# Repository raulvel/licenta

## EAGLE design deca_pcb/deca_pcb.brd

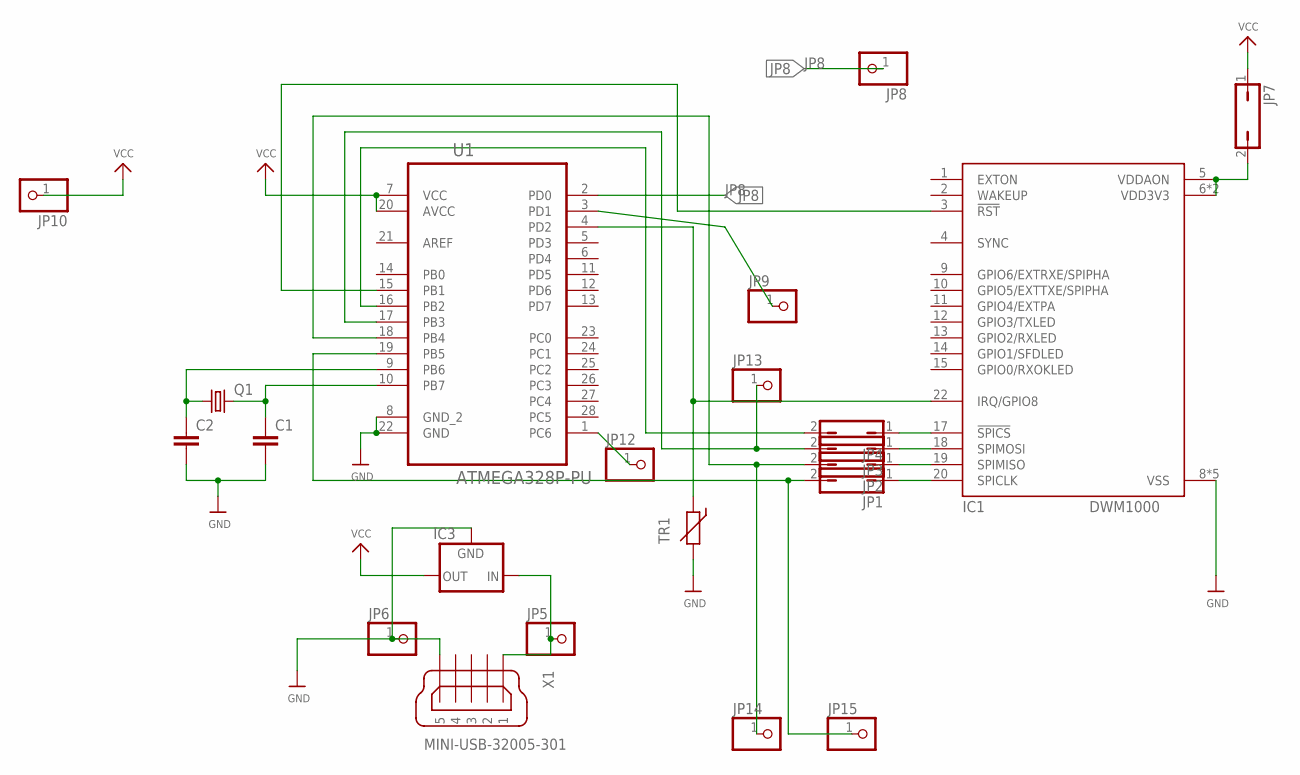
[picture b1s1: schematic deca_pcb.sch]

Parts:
C1, C2: C2.5/6; C2.5-6
IC1: DWM1000
IC3: LFXXCVS; TO220S
JP1, JP2, JP3, JP4, JP7: JP1Q; JP1
JP5, JP6, JP8, JP9, JP10, JP12, JP13, JP14, JP15: PINHD-1X1_2.54; 1X01
Q1: CRYSTALHC49S; HC49/S
TR1: THERMISTOR_R-5; R-5
U1: ATMEGA328P-PU; DIP254P762X457-28
X1: MINI-USB-32005-301; 32005-301

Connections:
GND: C1.2, C2.2, IC1.8 (VSS), IC1.16 (VSS), IC1.21 (VSS), IC1.23 (VSS), IC1.24 (VSS), IC3.2 (GND), JP6.1, TR1.2, U1.8 (GND_2), U1.22 (GND), X1.5
JP8: JP8.1, U1.2 (PD0)
unnamed: JP1.2, JP15.1, U1.19 (PB5)
unnamed: JP2.2, JP14.1, U1.18 (PB4)
unnamed: JP3.2, JP13.1, U1.17 (PB3)
unnamed: JP4.2, U1.16 (PB2)
unnamed: IC1.22 (IRQ/GPIO8), TR1.1, U1.4 (PD2)
unnamed: IC1.3 (!RST), U1.15 (PB1)
unnamed: C2.1, Q1.1, U1.9 (PB6)
unnamed: C1.1, Q1.2, U1.10 (PB7)
unnamed: IC1.5 (VDDAON), IC1.6 (VDD3V3), IC1.7 (VDD3V3), JP7.2
unnamed: IC3.1 (IN), JP5.1, X1.1
unnamed: IC1.20 (SPICLK), JP1.1
unnamed: IC1.19 (SPIMISO), JP2.1
unnamed: IC1.18 (SPIMOSI), JP3.1
unnamed: IC1.17 (!SPICS), JP4.1
unnamed: JP9.1, U1.3 (PD1)
unnamed: JP12.1, U1.1 (PC6)
VCC: IC3.3 (OUT), JP7.1, JP10.1, U1.7 (VCC), U1.20 (AVCC)

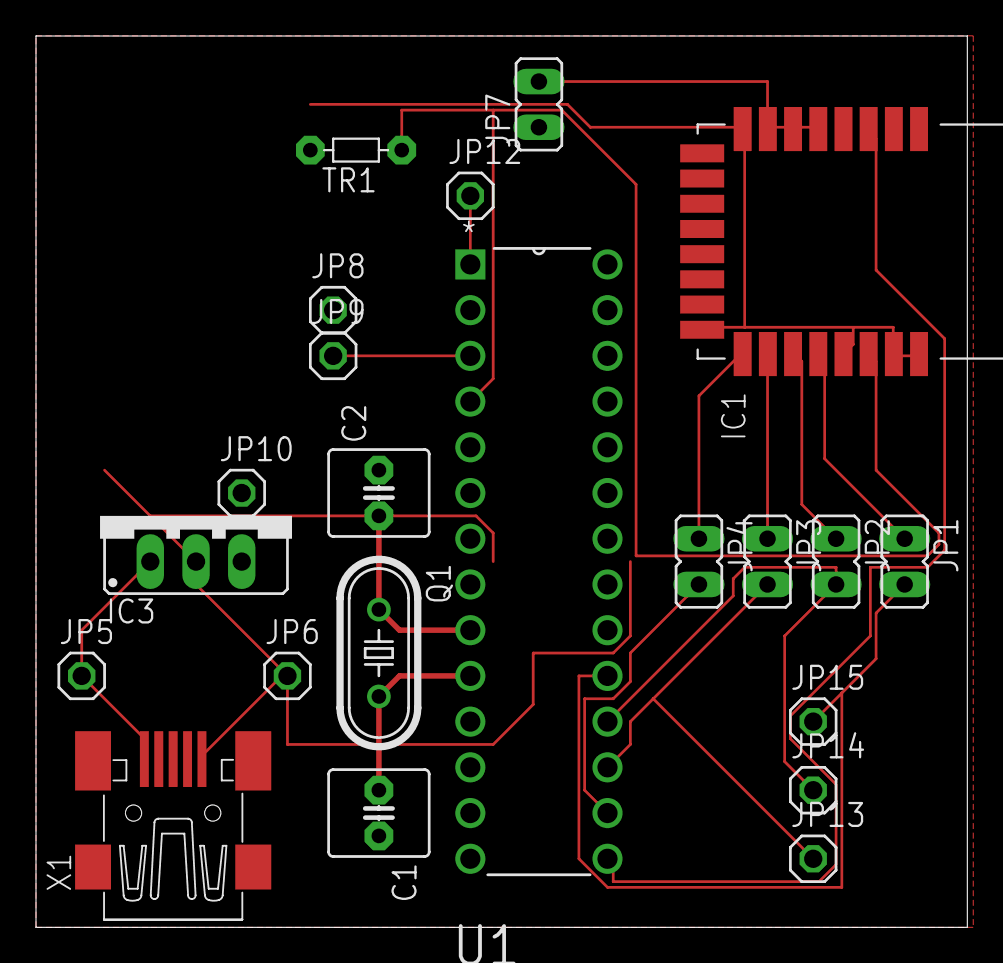
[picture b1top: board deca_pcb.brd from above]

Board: 2 copper layers, 51.7 x 49.5 mm, 22 parts (0 on the bottom side), 19 nets.

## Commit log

2019-04-12 resources
2019-04-12 initial deca pcb
2019-04-12 added connections from uC to DWM1000
2019-04-15 added components
2019-04-15 pdf sch
2019-04-16 docs
2019-04-18 board pcb done
2019-06-07 update ppt
2019-06-09 plot
2019-06-09 serial com
2019-06-10 added plot functions
2019-06-13 variants
2019-06-26 ty word
2019-07-03 filter
2019-07-06 done state of the art
2019-07-09 as
    as
2019-07-10 testing location

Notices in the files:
parts and their libraries:
microbuilder: This work is placed in the public domain, and may be freely used for commercial and non-commercial work with the following conditions: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
